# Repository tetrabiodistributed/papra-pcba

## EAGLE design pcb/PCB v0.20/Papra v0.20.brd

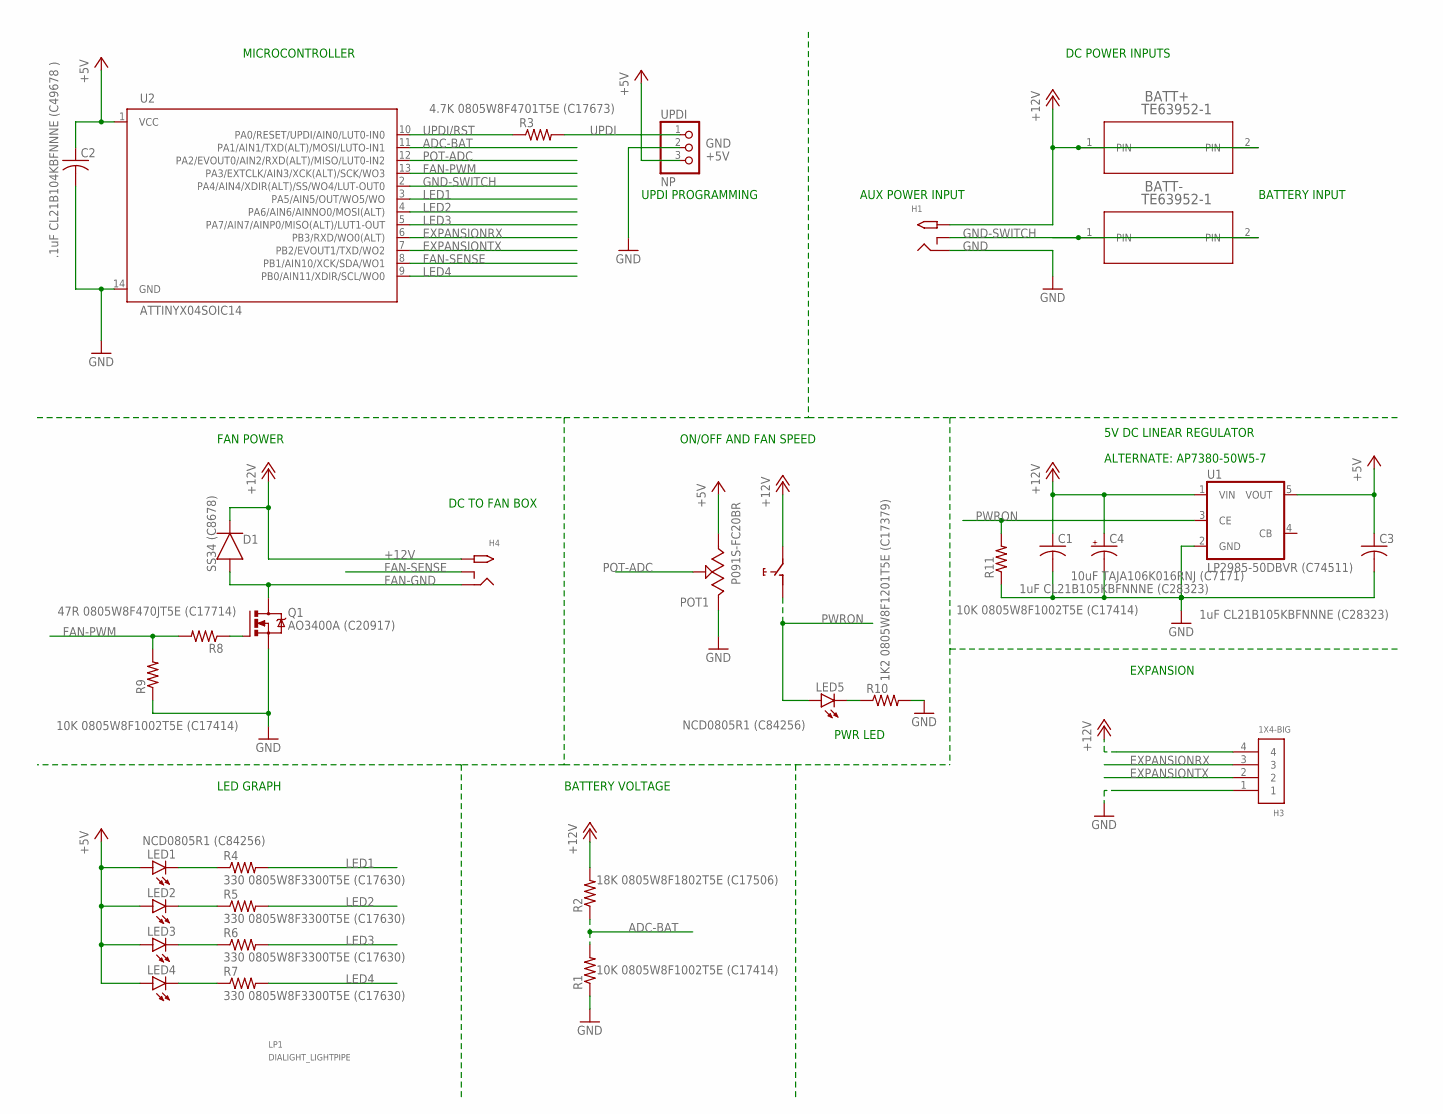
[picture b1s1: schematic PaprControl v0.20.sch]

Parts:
BATT+: TE63952-1
BATT-: TE63952-1
C1, C3: 1uF CL21B105KBFNNNE (C28323); C0805
C2: .1uF CL21B104KBFNNNE (C49678 ); C0805
C4: 10uF TAJA106K016RNJ (C7171); A/3216-18R
D1: SS34 (C8678); DIOM5226X290N
H1, H4: M-CUI-PJ-066A; DCJACK-PJ-066A
H3: 1X4-BIG; 1X04-BIG
LED1, LED2, LED3, LED4, LED5: NCD0805R1 (C84256); CHIPLED_0805
LP1: DIALIGHT_LIGHTPIPE; DIALIGHT_5151020F_/LEDS
POT1: P091S-FC20BR
Q1: AO3400A (C20917); SOT23
R1, R9, R11: 10K 0805W8F1002T5E (C17414); R0805
R2: 18K 0805W8F1802T5E (C17506); R0805
R3: 4.7K 0805W8F4701T5E (C17673); R0805
R4, R5, R6, R7: 330 0805W8F3300T5E (C17630); R0805
R8: 47R 0805W8F470JT5E (C17714); R0805
R10: 1K2 0805W8F1201T5E (C17379); R0805
U1: LP2985-50DBVR (C74511); SOT25
U2: ATTINYX04SOIC14; SOIC127P600X144-14
UPDI: NP; 1X03

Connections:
+5V: C2.1, C3.1, LED1.A, LED2.A, LED3.A, LED4.A, POT1.1, U1.5 (VOUT), U2.1 (VCC), UPDI.3
+12V: BATT+.1, BATT+.2, C1.1, C4.+, D1.1 (C), H1.PWR (TIP), H3.4, H4.PWR (TIP), POT1.NO (5), R2.2, U1.1 (VIN)
ADC-BAT: R1.2, R2.1, U2.11 (PA1/AIN1/TXD(ALT)/MOSI/LUTO-IN1)
EXPANSIONRX: H3.3, U2.6 (PB3/RXD/WO0(ALT))
EXPANSIONTX: H3.2, U2.7 (PB2/EVOUT1/TXD/WO2)
FAN-GND: D1.2 (A), H4.GND (RING), Q1.3 (D)
FAN-PWM: R8.2, R9.2, U2.13 (PA3/EXTCLK/AIN3/XCK(ALT)/SCK/WO3)
FAN-SENSE: H4.GNDBREAK (RING_SW), U2.8 (PB1/AIN10/XCK/SDA/WO1)
FETGATE: Q1.1 (G), R8.1
GND: C1.2, C2.2, C3.2, C4.-, H1.GND (RING), H3.1, POT1.3, Q1.2 (S), R1.1, R9.1, R10.2, R11.1, U1.2 (GND), U2.14 (GND), UPDI.2
GND-SWITCH: BATT-.1, BATT-.2, H1.GNDBREAK (RING_SW), U2.2 (PA4/AIN4/XDIR(ALT)/SS/WO4/LUT-OUT0)
LED1: R4.2, U2.3 (PA5/AIN5/OUT/WO5/WO)
LED1-R: LED1.C, R4.1
LED2: R5.2, U2.4 (PA6/AIN6/AINNO0/MOSI(ALT))
LED2-R: LED2.C, R5.1
LED3: R6.2, U2.5 (PA7/AIN7/AINP0/MISO(ALT)/LUT1-OUT)
LED3-R: LED3.C, R6.1
LED4: R7.2, U2.9 (PB0/AIN11/XDIR/SCL/WO0)
LED4-R: LED4.C, R7.1
LED5-R: LED5.C, R10.1
POT-ADC: POT1.2, U2.12 (PA2/EVOUT0/AIN2/RXD(ALT)/MISO/LUT0-IN2)
PWRON: LED5.A, POT1.COM (4), R11.2, U1.3 (CE)
UPDI: R3.2, UPDI.1
UPDI/RST: R3.1, U2.10 (PA0/RESET/UPDI/AIN0/LUT0-IN0)

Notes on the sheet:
AUX POWER INPUT
BATTERY INPUT
DC POWER INPUTS
5V DC LINEAR REGULATOR
ON/OFF AND FAN SPEED
FAN POWER
MICROCONTROLLER
LED GRAPH
BATTERY VOLTAGE
EXPANSION
DC TO FAN BOX
UPDI PROGRAMMING
PWR LED
ALTERNATE: AP7380-50W5-7

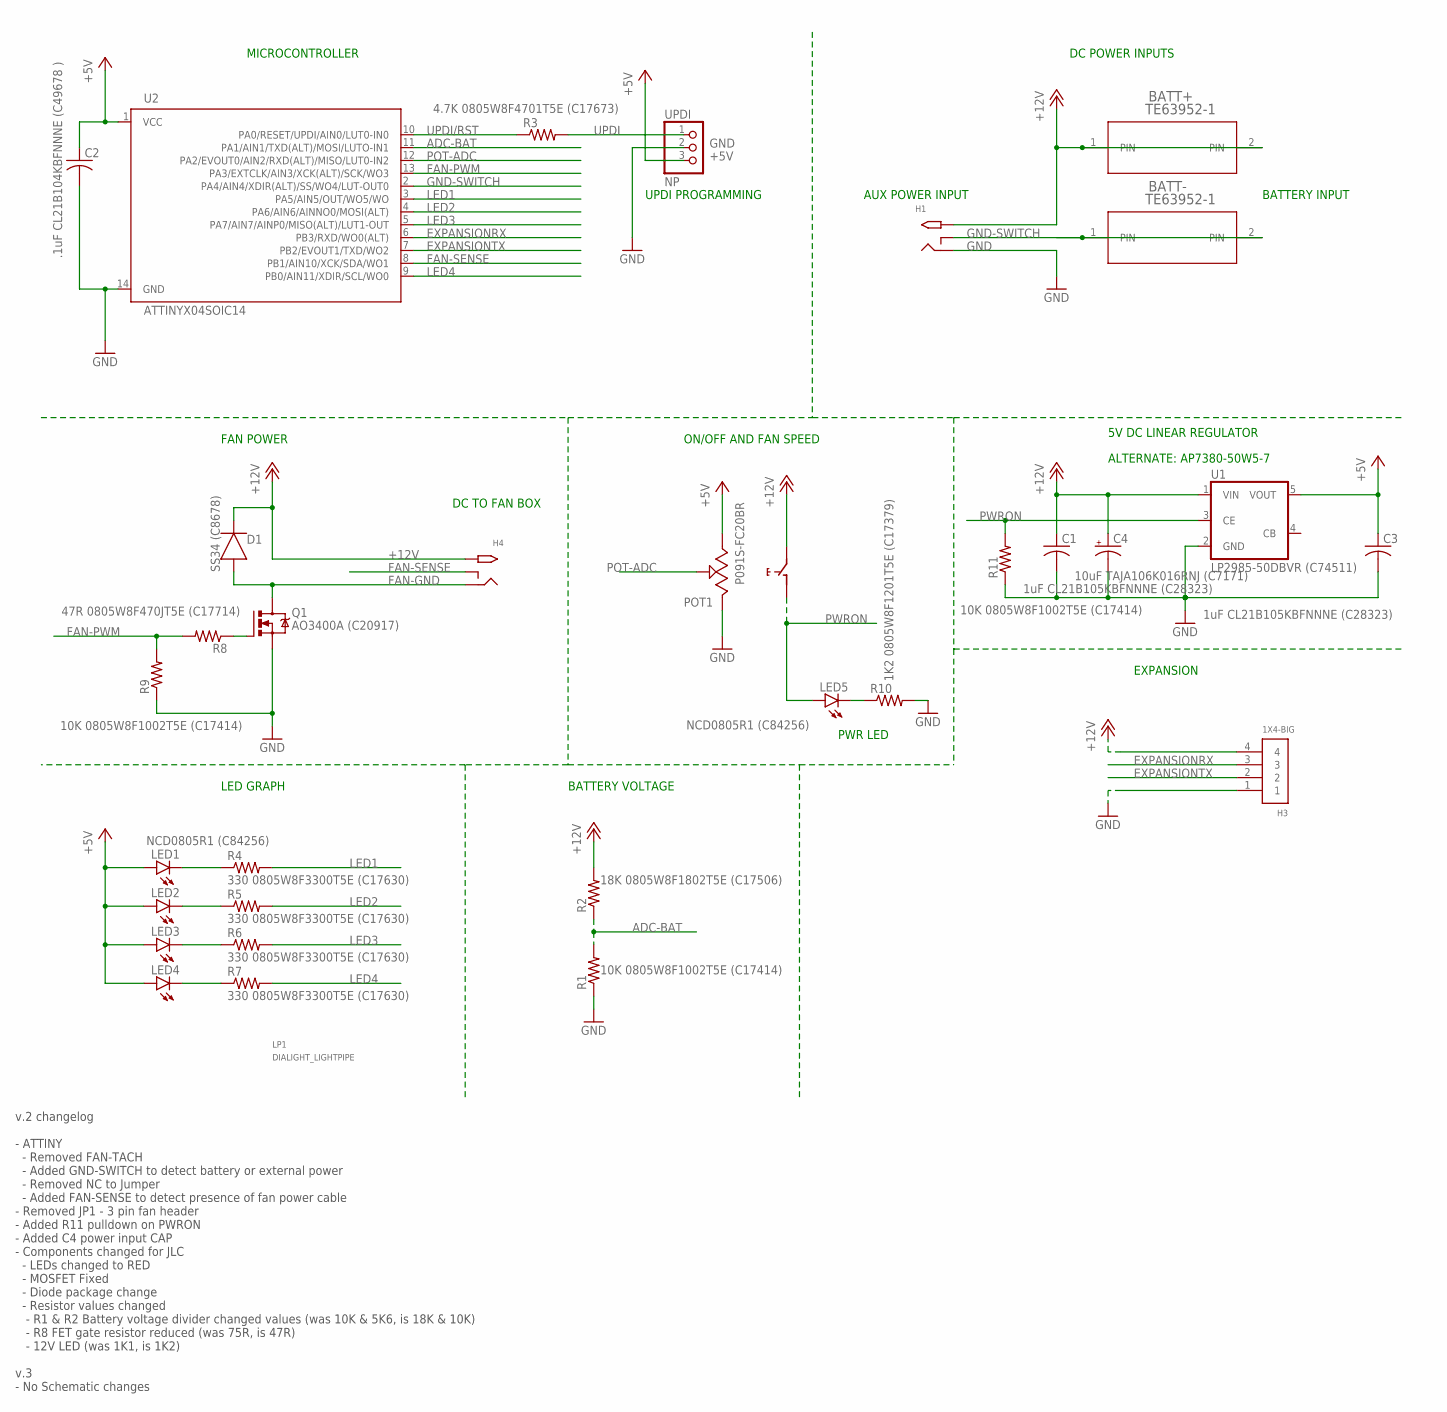
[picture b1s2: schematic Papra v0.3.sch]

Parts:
BATT+: TE63952-1
BATT-: TE63952-1
C1, C3: 1uF CL21B105KBFNNNE (C28323); C0805
C2: .1uF CL21B104KBFNNNE (C49678 ); C0805
C4: 10uF TAJA106K016RNJ (C7171); A/3216-18R
D1: SS34 (C8678); DIOM5226X290N
H1, H4: M-CUI-PJ-066A; DCJACK-PJ-066A
H3: 1X4-BIG; 1X04-BIG
LED1, LED2, LED3, LED4, LED5: NCD0805R1 (C84256); CHIPLED_0805
LP1: DIALIGHT_LIGHTPIPE; DIALIGHT_5151020F_/LEDS
POT1: P091S-FC20BR
Q1: AO3400A (C20917); SOT23
R1, R9, R11: 10K 0805W8F1002T5E (C17414); R0805
R2: 18K 0805W8F1802T5E (C17506); R0805
R3: 4.7K 0805W8F4701T5E (C17673); R0805
R4, R5, R6, R7: 330 0805W8F3300T5E (C17630); R0805
R8: 47R 0805W8F470JT5E (C17714); R0805
R10: 1K2 0805W8F1201T5E (C17379); R0805
U1: LP2985-50DBVR (C74511); SOT25
U2: ATTINYX04SOIC14; SOIC127P600X144-14
UPDI: NP; 1X03

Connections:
+5V: C2.1, C3.1, LED1.A, LED2.A, LED3.A, LED4.A, POT1.1, U1.5 (VOUT), U2.1 (VCC), UPDI.3
+12V: BATT+.1, BATT+.2, C1.1, C4.+, D1.1 (C), H1.PWR (TIP), H3.4, H4.PWR (TIP), POT1.NO (5), R2.2, U1.1 (VIN)
ADC-BAT: R1.2, R2.1, U2.11 (PA1/AIN1/TXD(ALT)/MOSI/LUTO-IN1)
EXPANSIONRX: H3.3, U2.6 (PB3/RXD/WO0(ALT))
EXPANSIONTX: H3.2, U2.7 (PB2/EVOUT1/TXD/WO2)
FAN-GND: D1.2 (A), H4.GND (RING), Q1.3 (D)
FAN-PWM: R8.2, R9.2, U2.13 (PA3/EXTCLK/AIN3/XCK(ALT)/SCK/WO3)
FAN-SENSE: H4.GNDBREAK (RING_SW), U2.8 (PB1/AIN10/XCK/SDA/WO1)
FETGATE: Q1.1 (G), R8.1
GND: C1.2, C2.2, C3.2, C4.-, H1.GND (RING), H3.1, POT1.3, Q1.2 (S), R1.1, R9.1, R10.2, R11.1, U1.2 (GND), U2.14 (GND), UPDI.2
GND-SWITCH: BATT-.1, BATT-.2, H1.GNDBREAK (RING_SW), U2.2 (PA4/AIN4/XDIR(ALT)/SS/WO4/LUT-OUT0)
LED1: R4.2, U2.3 (PA5/AIN5/OUT/WO5/WO)
LED1-R: LED1.C, R4.1
LED2: R5.2, U2.4 (PA6/AIN6/AINNO0/MOSI(ALT))
LED2-R: LED2.C, R5.1
LED3: R6.2, U2.5 (PA7/AIN7/AINP0/MISO(ALT)/LUT1-OUT)
LED3-R: LED3.C, R6.1
LED4: R7.2, U2.9 (PB0/AIN11/XDIR/SCL/WO0)
LED4-R: LED4.C, R7.1
LED5-R: LED5.C, R10.1
POT-ADC: POT1.2, U2.12 (PA2/EVOUT0/AIN2/RXD(ALT)/MISO/LUT0-IN2)
PWRON: LED5.A, POT1.COM (4), R11.2, U1.3 (CE)
UPDI: R3.2, UPDI.1
UPDI/RST: R3.1, U2.10 (PA0/RESET/UPDI/AIN0/LUT0-IN0)

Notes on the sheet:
AUX POWER INPUT
BATTERY INPUT
DC POWER INPUTS
5V DC LINEAR REGULATOR
ON/OFF AND FAN SPEED
FAN POWER
MICROCONTROLLER
LED GRAPH
BATTERY VOLTAGE
EXPANSION
DC TO FAN BOX
UPDI PROGRAMMING
PWR LED
ALTERNATE: AP7380-50W5-7
v.2 changelog - ATTINY - Removed FAN-TACH - Added GND-SWITCH to detect battery or external power - Removed NC to Jumper - Added FAN-SENSE to detect presence of fan power cable - Removed JP1 - 3 pin fan header - Added R11 pulldown on PWRON - Added C4 power input CAP - Components changed for JLC - LE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

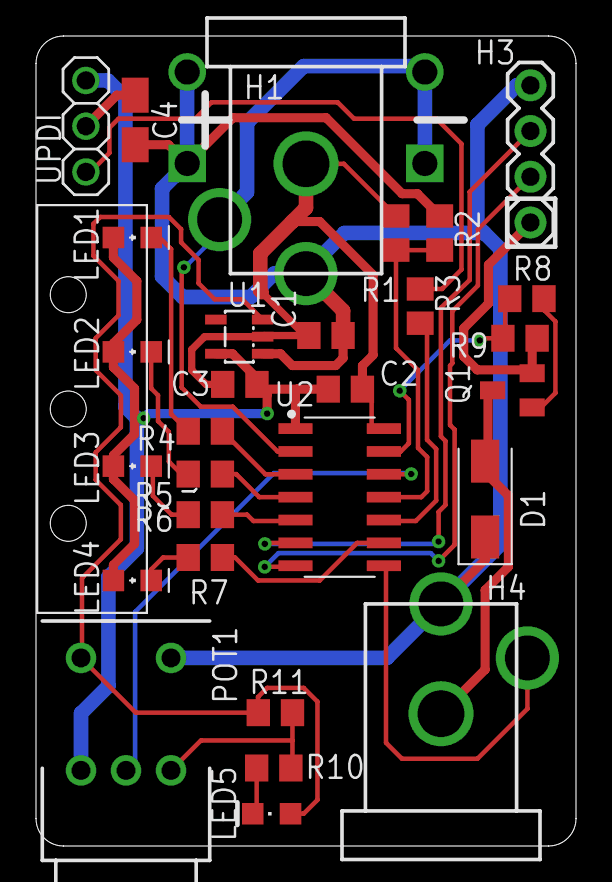
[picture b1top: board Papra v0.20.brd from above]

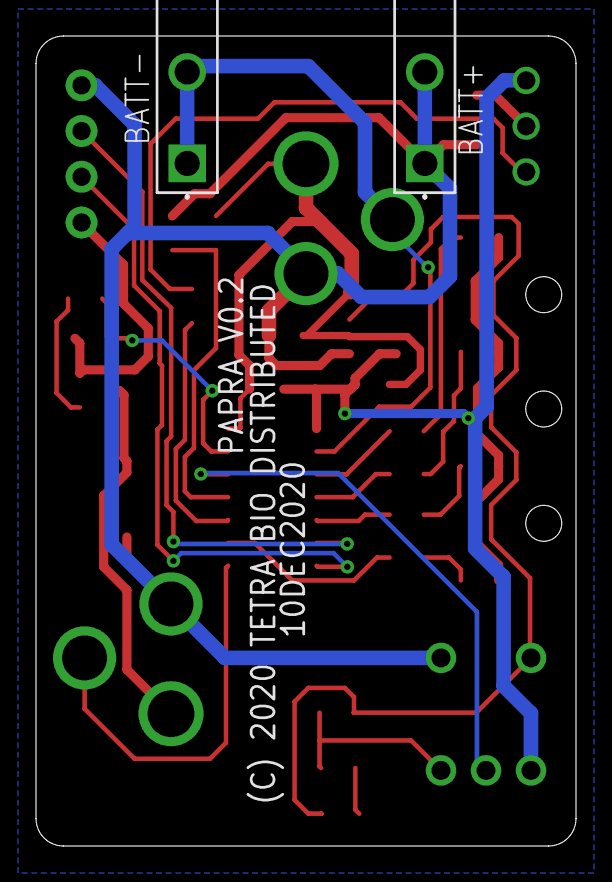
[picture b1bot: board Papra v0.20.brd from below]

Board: 2 copper layers, 30.0 x 45.0 mm, 32 parts (2 on the bottom side), 24 nets.

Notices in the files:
pcb/PCB v0.20/Papra v0.20.brd:
(C) 2020 TETRA BIO DISTRIBUTED
